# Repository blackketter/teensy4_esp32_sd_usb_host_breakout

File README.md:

# Teensy 4.0 ESP32 / USB Host / MicroSD Breakout Board

A jumbo breakout board with ESP32, USB-A host and microSD connectors to mate with the [Teensy 4 Header Breakout Board](https://github.com/blackketter/teensy4_header_breakout).

Additionally, the board includes a space for RTC Battery Holder and provides another Teensy reset/programming button (since it covers up the one on the Teensy).

It's designed to mount above or below the Teensy 4 and Header Breakout board on a relatively tall header.

Designed in KiCad.

### Notes:

- Status: Version 1.0 board ordered
- [OSHPark]() (https://oshpark.com/projects/xaSKCWHX)
- Download bom/ibom.html and view it with web browser to see bill of materials and placement information.

### Options

* Three jumpers on the back:
  * JP1 - Short to use Teensy 3.3v to power ESP32 (instead of onboard 3.3v regulator)
  * JP3 - Cut left side, bridge right side to disable D27 as USB Power Enable
  * JP2 - Cut to disable D29 as SD card detect

### Connectors
* J1 and J3 connect to the [Teensy 4 Header Breakout Board](https://github.com/blackketter/teensy4_header_breakout) pins via a header
* J5 is optional and provides access to the onboard 3.3v regulator
* J6 & J7 are optional and provide connection to the corresponding pins directly below on Teensy.  These connect the ESP32 SPI to the Teensy SPI port for high-speed goodness.  Should be compatible with the Adafruit Airlift firmware.
* J2 is a USB-A host connector
* J4 is a MicroSD push-pull connector

### Additional features
* Teensy programming button
* Socket for 12mm lithium backup batter for RTC
* RGB and White LEDs connected to ESP32 for additional status

**J1 - Left Side Pinout:**

1. Teensy D34 / SD DAT1
2. Teensy D35 / SD DAT0
3. GND
4. Teensy D36 / SD CLK
5. Teensy 3.3v
6. Teensy D37 / SD CMD
7. Teensy D38 / SD DAT3
8. Teensy D39 / SD DAT2
9. Teensy D29 / Card Detect
10. Teensy D31 (unused)
11. Teensy D33 (unused)
12. Teensy D32 (unused)
13. Teensy D30 (unused)
14. Teensy VBAT (battery backup)

**J3 - Right Side Pinout:**

1. Teensy VUSB
2. Teensy USB Host D-
3. Teensy USB Host D+
4. GND
5. GND
6. Teensy D27/USB Power EN
7. Teensy D25/ESP32 IO1 (Serial RX)
8. Teensy D26 / ESP32 IO0 (Boot Mode)
9. Teensy D28 / ESP32 EN (Reset)
10. Teensy D24 / ESP IO3 (Serial TX)
11. Teensy 3.3v
12. GND
13. Teensy Program
14. Teensy On/Off (unused)

**J5 - Optional additional pins**

15. GND
16. 3.3v from regulator on breakout board
17. ESP32 IO2
18. ESP32 IO4
19. ESP32 IO12
20. ESP32 IO13
21. ESP32 IO15
22. ESP32 IO16

**J6 - SPI between ESP32 and Teensy**

1. Teensy D9 / ESP32 IO32 (Busy)
2. Teensy D10 / ESP32 IO5 (CS)
3. Teensy D11 / ESP32 IO14 (MOSI)
4. Teensy D12 / ESP32 IO23 (MISO)

**J7 - SPI between ESP32 and Teensy (cont.)**

1. Teensy D13 / ESP32 IO18 (SCK)

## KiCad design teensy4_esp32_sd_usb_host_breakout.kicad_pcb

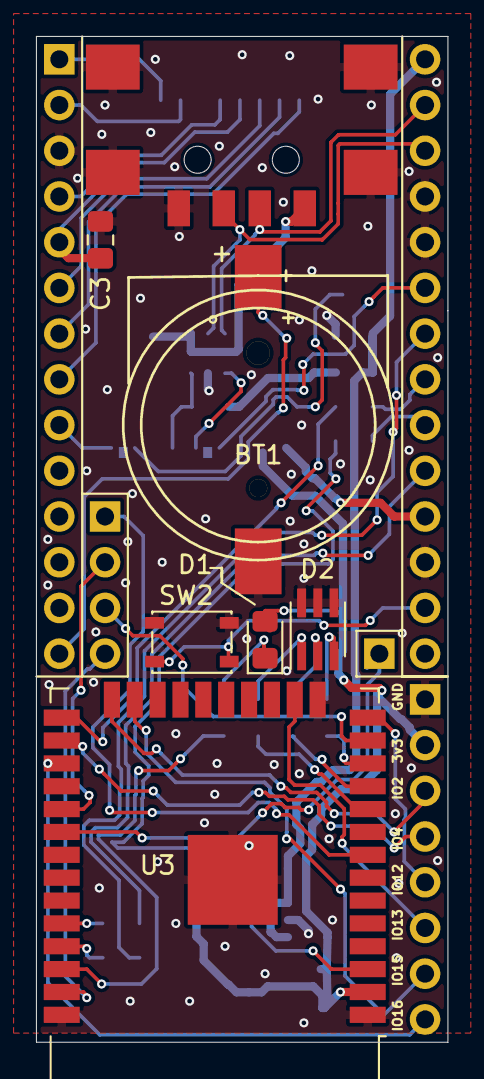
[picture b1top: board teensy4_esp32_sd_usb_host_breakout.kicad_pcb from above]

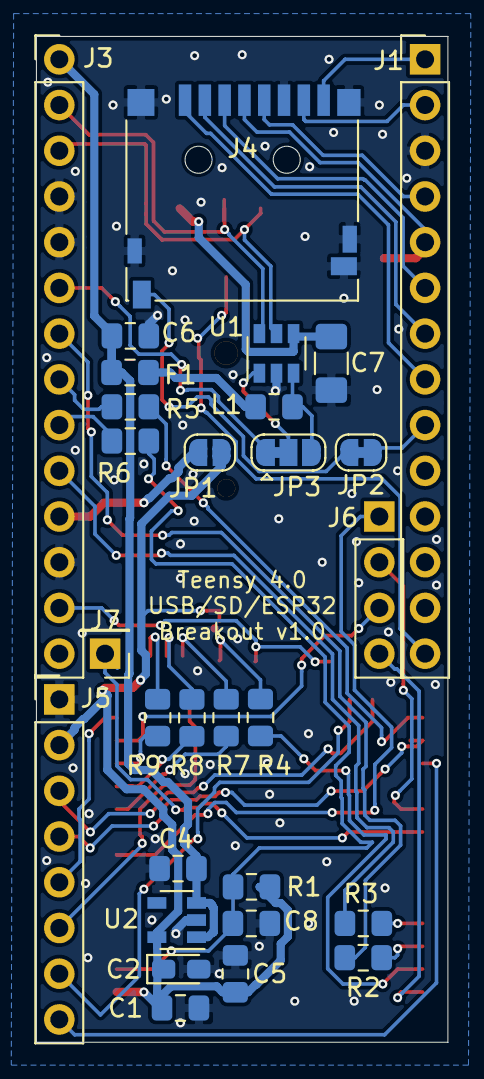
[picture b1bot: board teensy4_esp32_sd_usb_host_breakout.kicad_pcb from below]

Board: 2 copper layers, 22.9 x 55.9 mm, 36 parts (29 on the bottom side), 49 nets.

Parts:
BT1: Battery_Cell; BatteryHolder_MPD_BC501SM
C1: 0.1u/50v; C_0805_2012Metric_Pad1.15x1.40mm_HandSolder
C2: 22u/10v; CP_EIA-2012-12_Kemet-R_Pad1.30x1.05mm_HandSolder
C3: 10u; C_0805_2012Metric_Pad1.15x1.40mm_HandSolder
C4, C5, C8: 1u; C_0805_2012Metric_Pad1.15x1.40mm_HandSolder
C6: 2u2; C_0805_2012Metric_Pad1.15x1.40mm_HandSolder
C7: 100u; C_1206_3216Metric_Pad1.42x1.75mm_HandSolder
D1: LED; LED_0805_2012Metric_Pad1.15x1.40mm_HandSolder
D2: LED_RGB; LED_Avago_PLCC6_3x2.8mm
F1: 500mA; L_0805_2012Metric_Pad1.15x1.40mm_HandSolder
J1, J3: Conn_01x14; PinHeader_1x14_P2.54mm_Vertical
J2: USB_A; USB_A_Receptacle_SMD_Wuerth_629104190121_Narrow
J4: Micro_SD_Card_Det_Hirose_DM3AT; microSD_HC_Hirose_DM3D-SF
J5: Conn_01x08; PinHeader_1x08_P2.54mm_Vertical
J6: Conn_01x04; PinHeader_1x04_P2.54mm_Vertical
J7: Conn_01x01; PinHeader_1x01_P2.54mm_Vertical
JP1: Teensy 3.3; SolderJumper-2_P1.3mm_Open_RoundedPad1.0x1.5mm
JP2: Card Detect/29; SolderJumper-2_P1.3mm_Bridged_RoundedPad1.0x1.5mm
JP3: Power Enable/27; SolderJumper-3_P1.3mm_Bridged12_RoundedPad1.0x1.5mm
L1: ferrite 150; L_0805_2012Metric_Pad1.15x1.40mm_HandSolder
R1: 10k; R_0805_2012Metric_Pad1.15x1.40mm_HandSolder
R2, R3, R5, R6: 0R; R_0805_2012Metric_Pad1.15x1.40mm_HandSolder
R4: 2k; R_0805_2012Metric_Pad1.15x1.40mm_HandSolder
R7, R8, R9: 1k; R_0805_2012Metric_Pad1.15x1.40mm_HandSolder
SW2: PROGRAM; SW_SPST_PTS810
U1: TPD3S014; SOT-23-6
U2: TLV75733PDBVR; SOT-23-5
U3: ESP32-WROOM-32D; ESP32-WROOM-32

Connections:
+3V3: C1.1, C2.1, C5.1, D1.2, J5.2, JP1.2, R1.2, U2.5, U3.2
/3V3_SD: C3.2, J1.5, J4.4
/3V3_Teensy: J3.11, JP1.1
/24: J3.10, R3.2
/24_TX6: R3.1, U3.34
/25: J3.7, R2.2
/25_RX6: R2.1, U3.35
/26: J3.8, R5.2
/26_IO0: R5.1, U3.25
/27: J3.6, JP3.1
/28: J3.9, R6.2
/28_EN: C8.1, R1.1, R6.1, U3.3
/29: J1.9, JP2.1
/CLK: J1.4, J4.5
/CMD: J1.6, J4.3
/D+: J2.3, J3.3, U1.5
/D-: J2.2, J3.2, U1.6
/DAT0: J1.2, J4.7
/DAT1: J1.1, J4.8
/DAT2: J1.8, J4.1
/DAT3: J1.7, J4.2
/EN: JP3.2, U1.1
/IO2: J5.3, U3.24
/IO4: J5.4, U3.26
/IO5_CS: J6.2, U3.29
/IO12: J5.5, U3.14
/IO13: J5.6, U3.16
/IO14_MOSI: J6.3, U3.13
/IO15: J5.7, U3.23
/IO16: J5.8, U3.27
/IO18_SCK: J7.1, U3.30
/IO22: R4.1, U3.36
/IO23_MISO: J6.4, U3.37
/IO25_RED: R7.2, U3.10
/IO26_GREEN: R8.2, U3.11
/IO27_BLUE: R9.2, U3.12
/IO32_ESP_BUSY: J6.1, U3.8
/PROGRAM: J3.13, SW2.1
/SD_DET: J4.10, JP2.2
/VBAT: BT1.1, J1.14
/VBUS: C7.1, J2.1, U1.4
/VUSB: C4.1, C6.1, F1.2, J3.1, U2.1, U2.3
GND: BT1.2, C1.2, C2.2, C3.1, C4.2, C5.2, C6.2, C7.2, C8.2, D2.4, D2.5, D2.6, J1.3, J2.4, J2.5, J3.4, J3.5, J3.12, J4.6, J4.9, J4.11, J5.1, SW2.2, U1.2, U2.2, U3.1, U3.15, U3.38, U3.39
unnamed: D1.1, R4.2
unnamed: D2.1, R7.1
unnamed: D2.2, R8.1
unnamed: D2.3, R9.1
unnamed: F1.1, L1.1
unnamed: JP3.3, L1.2, U1.3

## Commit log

2020-03-08 first draft
2020-03-08 Pictures
2020-03-08 Second draft
2020-03-08 More details
2020-03-08 Update readme, fix via sizes
2020-03-09 Version 1.0 Ordered
